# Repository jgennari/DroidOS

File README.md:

# DroidOS

DroidOS is a Arduino based operating system for community built R2 units. It uses an SBUS-based RC receiver and an Arduino microcontroller to operate any number of extra functions on your droid.

## Bring your droid to life!

The DroidOS got us started in the right direction, however this project is just the starting point for us. It allows us to control lights and sound from the RC controller, but you can build anything on top of it. It's based on the Teensy LC development kit.

## Startup Sequence:  
The startup lives in the Arduino `setup` procedure. It follows this procedure:

* Initiate USB serial for debugging
* Initialize MP3 Player
* Initialize SBUS
* Confirm SBUS is communicating
* Check Mode Switch

During the setup, the status LED on the Teensy will be solid.

Any error will be annunciated via the status LED on the board. Short bursts indicate the failure mode, followed by no light for 1.5 seconds, repeated 3 times.

1. MP3 player initaliztion failed
2. Card online failed
3. Failed to count MP3 files
4. SBUS init failed, no serial control

Upon failure and notification the system will reset and re-enter the startup sequence.

## SBUS:
The SBUS library was sourced & slightly modified from [zendes](https://github.com/zendes/SBUS). We are using an FrSky X4R & X8R and are using inverted serial setup in Arduino. Once SBUS is connected and the main loop is running, any change to the SBUS first 6 channels will trigger a brief flash of the Teensy status LED.

## Questions/suggestions
If you have any questions or suggestions please feel free to reach out via GitHub or submit and issue.

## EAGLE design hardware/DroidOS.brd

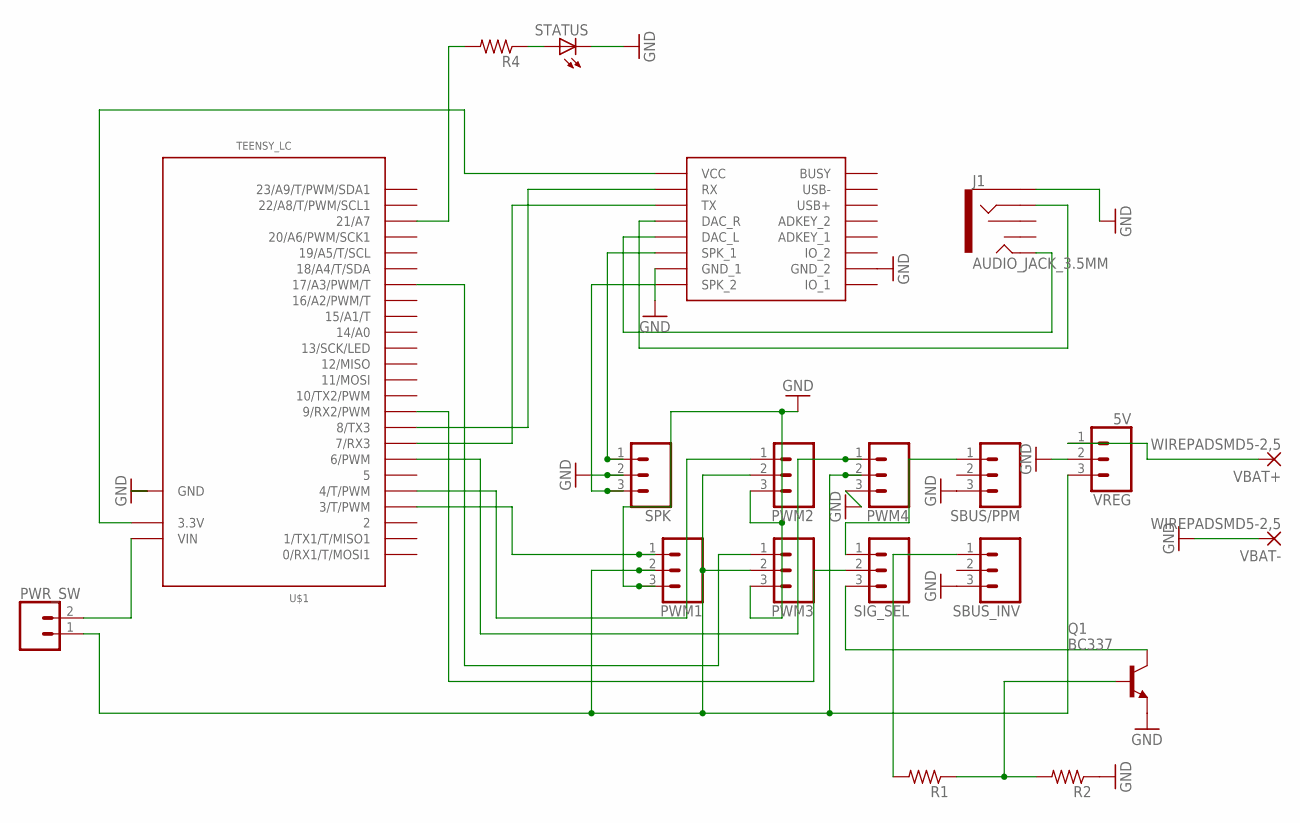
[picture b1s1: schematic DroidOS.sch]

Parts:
J1: AUDIO_JACK_3.5MM; AUDIO-JACK-KIT
PWM1, PWM2, PWM3, PWM4: CONN_03; 1X03
PWR_SW: CONN_02; 1X02
Q1: BC337; TO92
R1, R2, R4: R-US_R0805; R0805
SBUS/PPM: CONN_03; 1X03
SBUS_INV: CONN_03; 1X03
SIG_SEL: CONN_03; 1X03
SPK: CONN_03; 1X03
STATUS: LEDSML0805; SML0805
U$1: TEENSY_LC; TEENSY_3.0-3.2&LC_DIL
U$2: DFPLAYER
VBAT+: WIREPADSMD5-2,5; 5-2,5
VBAT-: WIREPADSMD5-2,5; 5-2,5
VREG: 5V; 1X03

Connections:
3V+: U$1.3.3V, U$2.VCC
5V: PWM1.2, PWM2.2, PWM3.2, PWM4.2, PWR_SW.1, VREG.3
AUD_RX: U$1.8 (8/TX3), U$2.RX
AUD_TX: U$1.7 (7/RX3), U$2.TX
CTRL_SIG: SIG_SEL.2, U$1.9 (9/RX2/PWM)
DAC_L: J1.TIP, U$2.DAC_L
DAC_R: J1.RING, U$2.DAC_R
GND: J1.SLEEVE, PWM1.3, PWM2.3, PWM3.3, PWM4.3, Q1.1 (E), R2.1, SBUS/PPM.3, SBUS_INV.3, SPK.2, STATUS.C, U$1.AGND (GND), U$1.GND, U$2.GND_1, U$2.GND_2, VBAT-.1, VREG.2
unnamed: PWR_SW.2, U$1.VIN
unnamed: R4.1, STATUS.A
unnamed: Q1.2 (B), R1.1, R2.2
PWM1_SIG: PWM1.1, U$1.3 (3/T/PWM)
PWM2_SIG: PWM2.1, U$1.4 (4/T/PWM)
PWM3_SIG: PWM3.1, U$1.17/A3 (17/A3/PWM/T)
PWM4_SIG: PWM4.1, U$1.6 (6/PWM)
SBUS_INV_IN: R1.2, SBUS_INV.1
SBUS_INV_OUT: Q1.3 (C), SIG_SEL.3
SBUS_OUT: SBUS/PPM.1, SIG_SEL.1
SPK_L: SPK.1, U$2.SPK1 (SPK_1)
SPK_R: SPK.3, U$2.SPK2 (SPK_2)
STATUS_LED: R4.2, U$1.21/A7
VBAT: VBAT+.1, VREG.1

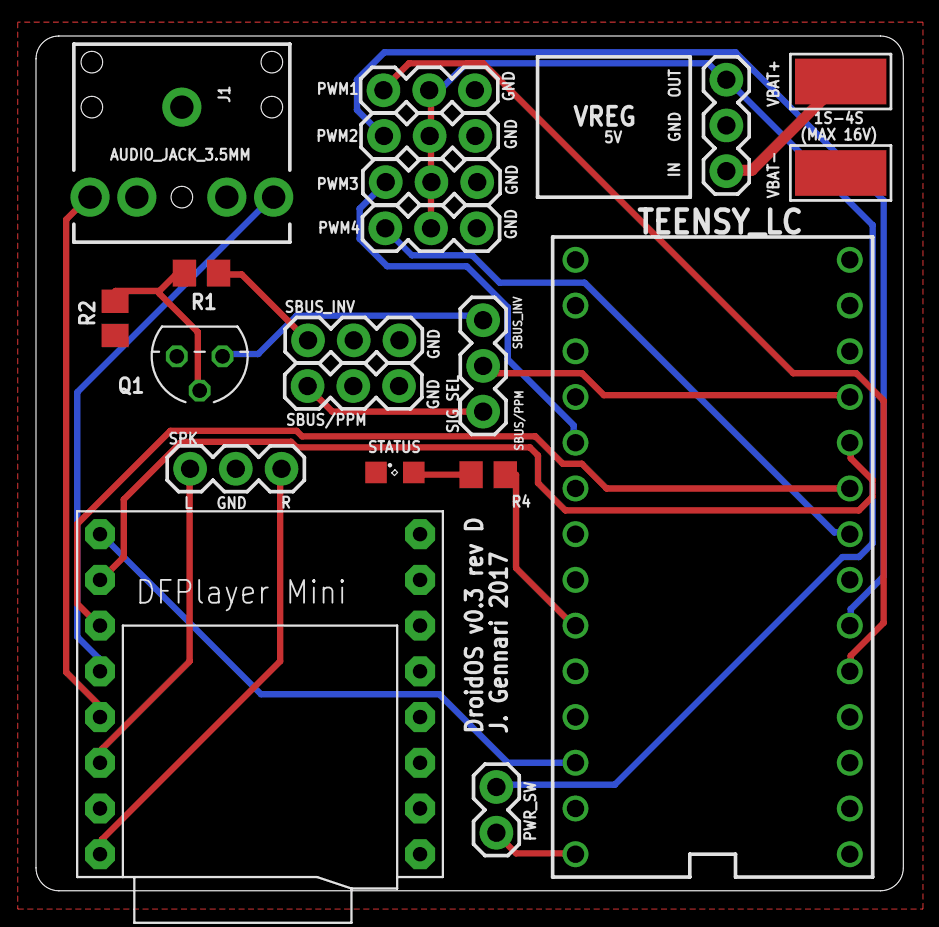
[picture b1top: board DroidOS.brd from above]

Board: 2 copper layers, 48.2 x 47.5 mm, 20 parts (0 on the bottom side), 22 nets.

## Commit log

2017-07-05 Added gitignore, changed system status
2017-07-05 Changed reset procedure
2017-07-05 Tweaked MP3 player failure handling
2017-07-05 Refactored reset code
2017-07-06 Allow serial control if no SBUS found.
2017-07-06 Add Windows build script
2017-07-06 Refactored timer code, stabilized audio
2017-07-06 Output formatting
2017-07-07 Lots of fixes, remote control, remote logging
2017-07-07 Added queue
2017-07-09 Rearranged SBUS, changed channel mapping
2017-10-17 Added support for Mega
2017-10-24 Added hardware files
2017-10-26 Added Eagle
2017-10-26 Changed layout
2017-10-27 v0.3
2017-11-17 Changed to Serial3 for Teensy LC
2017-11-18 Changes for Teensy
2017-12-05 Added nano source
2017-12-05 Reorged files
2017-12-05 Eagle arrangment
2017-12-07 Updated ino for Teensy/SBUS
2017-12-07 Added SBUS power out
2017-12-08 Updated code to show error blinks on boot
2017-12-08 Added image
2017-12-08 Added board to readme
2017-12-08 Added SBUS reference to readme'

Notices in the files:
parts and their libraries:
SparkFun-Connectors: Licensing: Creative Commons ShareAlike 4.0 International - https://creativecommons.org/licenses/by-sa/4.0
